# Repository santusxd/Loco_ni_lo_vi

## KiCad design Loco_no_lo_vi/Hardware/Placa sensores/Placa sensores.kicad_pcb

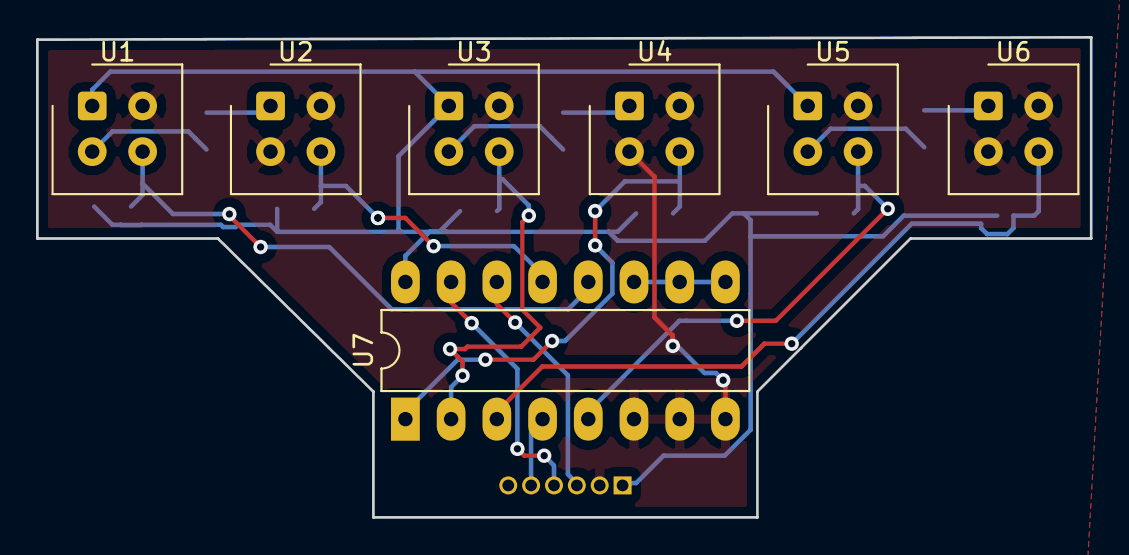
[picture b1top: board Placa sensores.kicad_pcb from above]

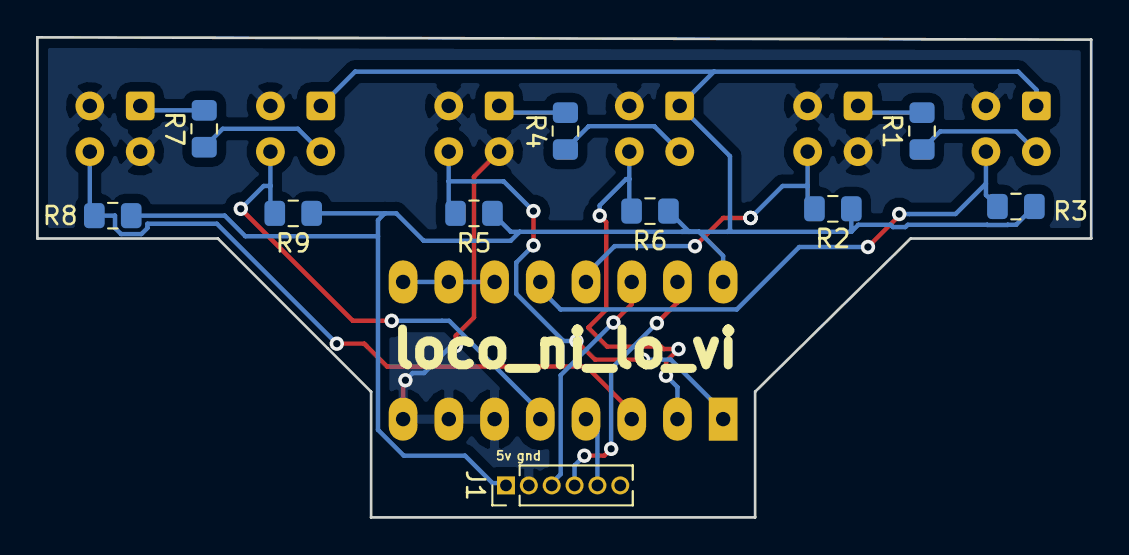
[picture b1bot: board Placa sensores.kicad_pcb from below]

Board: 2 copper layers, 58.5 x 26.7 mm, 17 parts (10 on the bottom side), 18 nets.

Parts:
J1: Conn_01x06_Female; PinHeader_1x06_P1.27mm_Vertical
R1, R4, R7: 82; R_0805_2012Metric_Pad1.15x1.40mm_HandSolder
R2, R3, R5, R6, R8, R9: 10k; R_0805_2012Metric_Pad1.15x1.40mm_HandSolder
U1, U2, U3, U4, U5, U6: CNY70; Vishay_CNY70
U7: 4053; DIP-16_W7.62mm_LongPads

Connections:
+5V: J1.1, R2.1, R3.1, R5.1, R6.1, R8.1, R9.1, U1.1, U3.1, U5.1, U7.16
/linea1: J1.3, U7.14
/linea2: J1.4, U7.15
/linea3: J1.5, U7.4
/linea_selc: U7.9, U7.10, U7.11
/sensor1: R3.2, U1.3, U7.12
/sensor2: R2.2, U2.3, U7.13
/sensor3: R6.2, U3.3, U7.2
/sensor4: R5.2, U4.3, U7.1
/sensor5: R9.2, U5.3, U7.5
/sensor6: R8.2, U6.3, U7.3
GND: J1.2, U1.4, U2.2, U2.4, U3.4, U4.2, U4.4, U5.4, U6.2, U6.4, U7.6, U7.7, U7.8
unnamed: R1.1, U1.2
unnamed: R1.2, U2.1
unnamed: R4.1, U3.2
unnamed: R4.2, U4.1
unnamed: R7.1, U5.2
unnamed: R7.2, U6.1

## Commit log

2018-11-17 Esquema y un poco de ki
2018-11-17 Esquema
2018-11-24 Terminé de enrutar y no he puesto los tornillos
2018-12-01 Parte del core (esquema)
2018-12-15 Más esquema
